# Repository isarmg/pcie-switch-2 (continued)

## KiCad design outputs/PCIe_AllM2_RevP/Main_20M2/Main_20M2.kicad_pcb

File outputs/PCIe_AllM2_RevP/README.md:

# Rev P：120 × 45 mm，20 个竖直 M.2，中心距 6 mm

本版按最新要求将插槽中心间距改为 **6 mm**。在 120 × 45 mm 板框、同面竖直且全部平行的条件下，一排放入 **20 个 M-Key 2280 插槽**；中心坐标为 X=3、9、15……117 mm，Y=23.3 mm。连接器行包络 X=0.825–119.175 mm、Y=11.025–35.575 mm。第 21 个连接器需要 120 mm 的中心跨度，会超出板框，故不保留上一试排的 27 槽数量。

**这是可编辑的布局、网络分配和供电预留草案。大部分线路、CPU 平台供电/时序、固件、阻抗和散热尚未完成，不能直接投产。**

## 2026-10-18：恢复检查点 1（仍不可上电）

- 补齐 M1–M4 的 R3005/R3015/R3025/R3035，100 kΩ 下拉；16 个 F.Cu–In1.Cu 相邻层微孔和 20 段 In1.Cu 铜线，原生连通检查确认每组连接器 pin50 → 电阻 → 本连接器 pin51。**该局部地簇仍未接入输入地，且没有复位释放驱动；不能据此宣称已实现上电复位。** 微孔填孔/叠层工艺尚待板厂确认。
- PCB 与原理图使用 KiCad 10 原生 netlist 精确同步，逐脚双向核验且禁止拆分/合并网络；原始 510 个铜对象的几何与电气归属不变。恢复原理图缺失的厂家链接，padless JHL9580 明确标为仅 PCB 机械占位。
- 修正继承自 E1.S 的错误网类覆盖：512 个数据网络、50 个时钟网络匹配对应草案网类；原有数字规则不变，不代表阻抗已验证。
- 按 TI 引脚表补正 U31/TPS62132、U605/TPS3808 及四颗 TPS565201 的 47 个脚的 ERC 类型，没有新增 PWR_FLAG、NC 标记或排除项。ERC 因真实未供电问题增加到 **47 错误、104 警告**，这些问题仍未解决。
- KiCad 10.0.7 原生 DRC：**几何 0，原理图/PCB parity 0**；499 条未连线是截断报告。全焊盘物理连通检查覆盖 7,558 个编号焊盘形状、7,540 个 ref.pin，确认 **891 个非 NC 网络中有 749 个断网**，不能将 499 当成实际未连线总数。
- U605 的 MR 仍接 1.8 V CPU 信号，而 VDD 为 3.3 V，尚缺正确电压域方案；CPU/PEX 的 1.8 V 电源也没有可证明完整的供电实现。不能照搬另一个设计的复位来源。

最新证据见 [VALIDATION.json](VALIDATION.json) 及 [checkpoint1 原生报告](review_2026-10-18/checkpoint1/REVIEW.json)。旧 STEP、装配图和预览仍是更改前的机械资料，未用于此检查点验收。历史构建器依赖原工作目录，可能覆盖本次 ECO，**不要运行 p_build/p_pipeline 重新生成当前修订**；本次增量脚本与验证器在 scripts/revP 下，详见 [修复记录](ELECTRICAL_REVIEW_2026-10-18.md)。

## 保留布局与槽位

- 主板 120 × 45 mm、32 铜层、名义厚度 1.6 mm，无 E1.S、子板、板间线缆和四角固定孔。
- CPU、PEX88096、USB-C、JHL9580 占位以及原平台器件共 **233 个器件保留原坐标、朝向和安装面**。M.2、新增供电器件以及 40 个端部槽位无源器件按 6 mm 间距重新排布，避免原交流耦合电容与新插槽位置相撞。
- M1/M2 位于 X=3/9 mm，N01–N16 位于 X=15–105 mm，M3/M4 位于 X=111/117 mm。所有插槽 F 面朝上、竖直且方向相同。
- 20 槽各保留 x4 网络分配，CPU 上行 x4；使用主数据 lane 0–83，84–95 共 12 lane 暂空。现有数据 lane 足以分配给全部 20 槽，因此本版没有额外仅供电槽。**没有为新增数量而补画协议铜线；PCIe/时钟大部分仍处于网络分配阶段。** switch 端口固件尚未配置。[Broadcom PEX88096](https://www.broadcom.com/products/pcie-switches-retimers/expressfabric/gen4/pex88096)
- 三颗 9ZXL0851 保留。第三颗仅使用五对输出给 N12–N16，其余三对悬空。CPU 的 ICC/BIOS、SSC/common-clock 和时钟启用配置仍待验证。

## 连接器与机械边界

M.2 和 USB-C 的金属固定脚均为 SMT。USB-C 每个端口的两个塑胶定位孔保留；M.2 取消定位柱孔，避免与背面 BGA 球阵冲突。

M.2 是参考 Amphenol MDT350M01001VT 的 **无定位柱自定义封装草案**，带柱原型号不能不经修改直接安装，实际无柱器件/去柱方案以及触点编号方向均待厂家确认。连接器以 Gen4 为参考，整条通道尚未验证。[Amphenol 参考器件](https://www.amphenol-cs.com/product/mdt350m01001vt.html)

USB-C 的四个 SMT 金属固定脚也是自定义草案，原 USB4160 穿板脚型号不兼容；TB5 连接器和通道资格尚未确认。JHL9580 仍为未核实的机械占位，按用户要求暂缓其电气设计。

switch 面器件高度按 ≤8 mm、连接器面 ≤9 mm；新增 TPSM53604 为最大 4.1 mm 的简化闭合包络。STEP 装配中的 SSD 为竖直的 2280 裸板/元件简化模型，散热器、外接插头和保持架另计。

## 12 V 输入与每槽 4 A 预留

按每槽 **3.3 V / 4 A**，20 槽共 **80 A、264 W** SSD 输出预算。原四个端部插槽保留独立 TPS565201；新增 16 槽各配一套真实 15 针封装的 TPSM53604RDAR、输入/输出电容和反馈分压。

TPSM53604 采用 10 kΩ / 4.32 kΩ，两个 10 µF / 50 V 输入电容、100 nF 旁路和四个 47 µF / 10 V 输出电容。3.3 V 需要至少 52 µF 有效输出电容，188 µF 为标称合计，偏压/温度降容仍未核对。DNC 4/5 独立悬空，V5V 不给外部供电。[TI SNVSBC9C](https://www.ti.com/lit/ds/symlink/tpsm53604.pdf)

输入仍保留 **12 V / 50 A、两个 25 A 支路**的设计目标。按 85% 换算效率及 85 W 平台余量，计算输入预算约 33 A。**模块和供电器件已落位、网络已分配，整板配电铜箔及电源回路仍未布完；输入焊盘、铜厚、线材、保险丝实物、过孔和满载散热能力均未验证。** 自定义 USB 外形供电口仍非 USB/PD，未接通主大电流母线；任何 M.2 电源脚均不接 12 V。

## 电气完成度

CPU 使用 Intel 官方的 2833 个非均匀球位，PEX88096 为真实 1550 球，几何逐球核对。CPU 0.25 mm 焊盘仍待装联图 751493 确认，多路 PMIC、启动时序、EC/BIOS、PDN 尚未完成。

仅保留原 CPU–PEX 的 8 对数据差分线和 1 对参考时钟，共 34 个电容分段铜线网络；其端点连接已经检查。20 槽的大部分协议和电源铜线、等长、阻抗、封装延迟补偿、HDI 工艺和整板 SI 均未完成。新增数据槽的 PERST 暂由下拉保持复位，复位驱动和时序尚未实现，不能宣称可枚举。

KiCad 的几何检查、未连线报告和原理图错误分别保存。短路/间距检查通过不等于电气设计已完成；`ERC.json` 如实保留尚未驱动的电源/控制输入等问题。

## 文件

- `Main_20M2/Main_20M2.kicad_pro`：本机 KiCad 可编辑工程。
- `Main_20M2/Main_20M2.step`：主板与器件；`Assembly_View/Assembly_View.step`：主板与 20 块竖直 2280 简化模型。
- `M2_PORTS.json`、`PORT_PLAN.csv`、`BOM.csv`、`Main_20M2/PIN_MAP.csv`：用途、真实 lane 分配、器件与逐脚网络。
- `CORE_PLACEMENT_BASELINE.json`、`VALIDATION.json`：保留器件、6 mm 间距、球位、原理图/PCB 网络与 lane 分配核验。
- `STEP_VALIDATION.json`：本机 KiCad 导入/再导出 STEP 的结果；`SHA256SUMS.txt`：归档哈希。

历史版本保留：Rev M 为 110 × 45 mm、10 E1.S + 4 M.2；Rev N 为 120 × 45 mm、23 M.2；27 槽的 Rev O 仅为已被本次 6 mm 间距要求取代的试排，未完成电气/STEP核验。本版不生成生产 Gerber 或钻孔包。

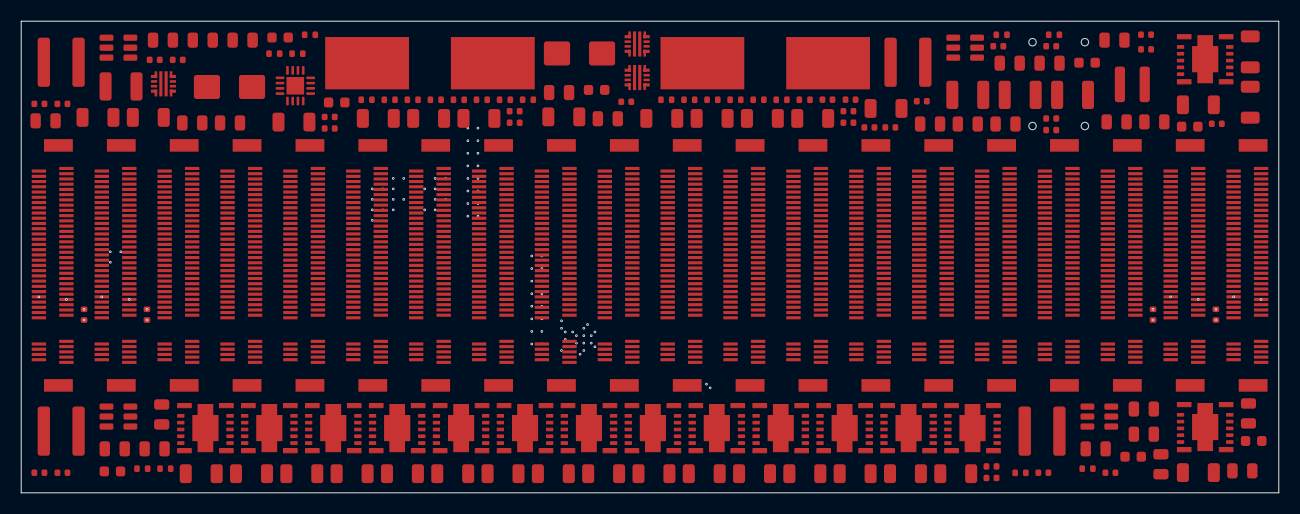
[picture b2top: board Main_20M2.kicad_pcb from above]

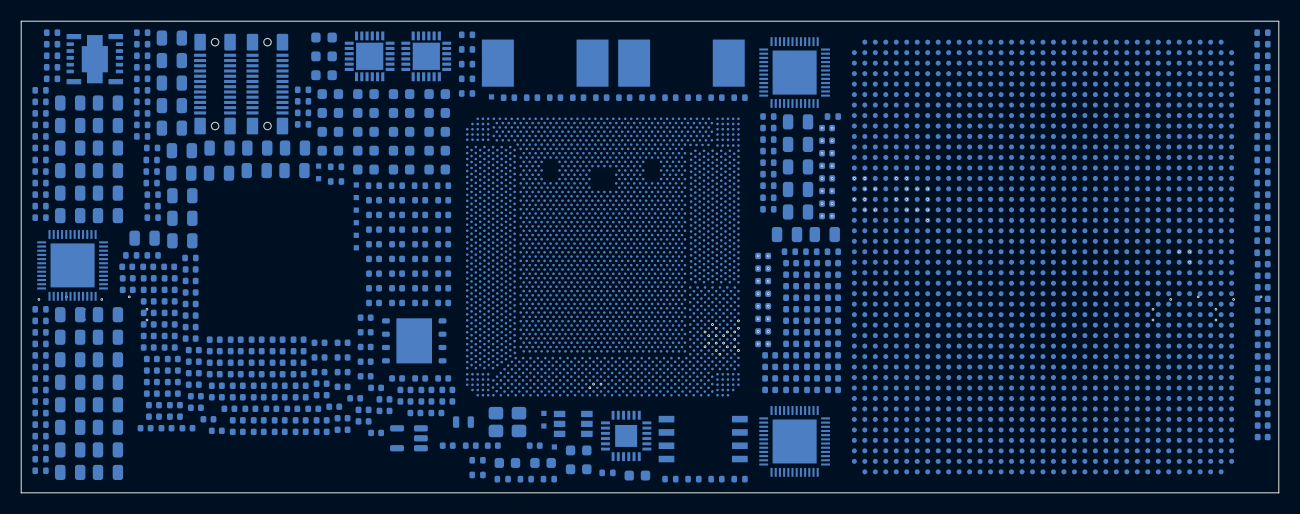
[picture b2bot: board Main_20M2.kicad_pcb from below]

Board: 32 copper layers, 120.0 x 45.0 mm, 647 parts (469 on the bottom side), 787 nets.

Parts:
C1, C2: 10uF 25V X7R; C_1210_3225Metric
C301: 10nF 25V; C_0402_1005Metric
C311: 10uF 25V; C_0805_2012Metric
C312, C3002, C3012, C3022, C3032, C5023, C5043, C5063, C5083, C5103, C5123, C5143, C5163, C5183, C5203, C5223, C5243, C5263, C5283, C5303, C5323: 100nF 50V; C_0402_1005Metric
C313: 3.3nF 25V; C_0402_1005Metric
C314, C315: 47uF 16V; C_1210_3225Metric
C411, C421: 10nF; C_0402_1005Metric
C412, C422: 100nF 50V; C_0603_1608Metric
C701, C720, C721, C722, C723, C724, C725, C726, C727, C728, C730, C731, C732, C733, C734, C735, C736, C737, C738, C742, C6501, C6502, C6503, C6504, C6505, C6506, C6507, C6508, C6509, C6510: 100nF; C_0402_1005Metric
C702, C707, C708: 1uF; C_0402_1005Metric
C703, C704: 18pF DNP TUNE; C_0402_1005Metric
C705, C706: 8.2pF DNP TUNE; C_0402_1005Metric
C709, C710: 100nF RC reset draft; C_0402_1005Metric
C741: 47nF / reset delay; C_0402_1005Metric
C801, C802, C803, C804, C805, C806, C807, C808, C811, C812, C813, C814, C815, C816, C817, C818: 220nF 6.3V X5R; C_0402_1005Metric
C901, C903, C905, C907, C909, C911, C913, C915, C917, C919, C921, C923, C925, C927, C929, C931, C933: 100nF / PDN budget; C_0402_1005Metric
C902, C904, C906, C908, C910, C912, C914, C916, C918, C920, C922, C924, C926, C928, C930, C932, C934: 4.7uF / PDN budget; C_0603_1608Metric
C951, C952, C953, C954, C955, C956, C957, C958, C959, C960: 4.7uF / EDGECAP value pending PDG; C_0603_1608Metric
C965, C966, C967, C968: 1uF / filter value pending PDG; C_0402_1005Metric
C3001, C3011, C3021, C3031: 10uF 25V X7R; C_0805_2012Metric
C3003, C3013, C3023, C3033: 100nF 25V; C_0402_1005Metric
C3004, C3005, C3014, C3015, C3024, C3025, C3034, C3035: 22uF 10V X5R / DC-bias review pending; C_0805_2012Metric
C3006, C3016, C3026, C3036: 1uF 16V; C_0603_1608Metric
C3051, C3052, C3053, C3054, C3055, C3056, C3057, C3058, C3061, C3062, C3063, C3064, C3065, C3066, C3067, C3068, C3071, C3072, C3073, C3074, C3075, C3076, C3077, C3078, C3081, C3082, C3083, C3084, C3085, C3086, C3087, C3088, C6011, C6012, C6013, C6014, C6015, C6016, C6017, C6018, C6021, C6022, C6023, C6024, C6025, C6026, C6027, C6028, C6031, C6032, C6033, C6034, C6035, C6036, C6037, C6038, C6041, C6042, C6043, C6044, C6045, C6046, C6047, C6048, C6051, C6052, C6053, C6054, C6055, C6056, C6057, C6058, C6061, C6062, C6063, C6064, C6065, C6066, C6067, C6068, C6071, C6072, C6073, C6074, C6075, C6076, C6077, C6078, C6081, C6082, C6083, C6084, C6085, C6086, C6087, C6088, C6091, C6092, C6093, C6094, C6095, C6096, C6097, C6098, C6101, C6102, C6103, C6104, C6105, C6106, C6107, C6108, C6111, C6112, C6113, C6114, C6115, C6116, C6117, C6118, C6121, C6122, C6123, C6124, C6125, C6126, C6127, C6128, C6131, C6132, C6133, C6134, C6135, C6136, C6137, C6138, C6141, C6142, C6143, C6144, C6145, C6146, C6147, C6148, C6151, C6152, C6153, C6154, C6155, C6156, C6157, C6158, C6161, C6162, C6163, C6164, C6165, C6166, C6167, C6168: 220nF 16V AC; C_0402_1005Metric
C5021, C5022, C5041, C5042, C5061, C5062, C5081, C5082, C5101, C5102, C5121, C5122, C5141, C5142, C5161, C5162, C5181, C5182, C5201, C5202, C5221, C5222, C5241, C5242, C5261, C5262, C5281, C5282, C5301, C5302, C5321, C5322: 10uF 50V / GRT31CR61H106ME01L; C_1206_3216Metric
C5024, C5025, C5026, C5027, C5044, C5045, C5046, C5047, C5064, C5065, C5066, C5067, C5084, C5085, C5086, C5087, C5104, C5105, C5106, C5107, C5124, C5125, C5126, C5127, C5144, C5145, C5146, C5147, C5164, C5165, C5166, C5167, C5184, C5185, C5186, C5187, C5204, C5205, C5206, C5207, C5224, C5225, C5226, C5227, C5244, C5245, C5246, C5247, C5264, C5265, C5266, C5267, C5284, C5285, C5286, C5287, C5304, C5305, C5306, C5307, C5324, C5325, C5326, C5327: 47uF 10V / GRM21BR61A476ME15L / DC-BIAS REVIEW; C_0805_2012Metric
C6511: 4.7uF 10V; C_0603_1608Metric
C6512: 1uF 10V; C_0603_1608Metric
D1, D2: SMBJ13CA; D_SMB
F1, F2: 25A FUSE / MPN AND THERMAL REVIEW TBD; Littelfuse_456_20A
J11, J12: 12V 25A FEED / DESIGN TARGET, COPPER AND CABLE TBD; WireSolder_2x_8x5_P12
J401: CUSTOM 12V POWER / SMT SHELL DRAFT; USB_C_24P_Vertical_SMT_Shell_7p46_CUSTOM_DRAFT
J402: TB5 PORT / SMT SHELL DRAFT / PART TBD; USB_C_24P_Vertical_SMT_Shell_7p46_CUSTOM_DRAFT
J501: M1 SSD / VERTICAL M-Key 2280 / NO-PEG DRAFT; MKey_Vertical_Gen4_24p2x3p5_NoLocatingPegs_DRAFT
J502: M2 SSD / VERTICAL M-Key 2280 / NO-PEG DRAFT; MKey_Vertical_Gen4_24p2x3p5_NoLocatingPegs_DRAFT
J503: M3 SSD / VERTICAL M-Key 2280 / NO-PEG DRAFT; MKey_Vertical_Gen4_24p2x3p5_NoLocatingPegs_DRAFT
J504: M4 SSD / VERTICAL M-Key 2280 / NO-PEG DRAFT; MKey_Vertical_Gen4_24p2x3p5_NoLocatingPegs_DRAFT
J6001: N01 M-Key 2280 / x4 / NO-PEG DRAFT; MKey_Vertical_Gen4_24p2x3p5_NoLocatingPegs_DRAFT
J6002: N02 M-Key 2280 / x4 / NO-PEG DRAFT; MKey_Vertical_Gen4_24p2x3p5_NoLocatingPegs_DRAFT
J6003: N03 M-Key 2280 / x4 / NO-PEG DRAFT; MKey_Vertical_Gen4_24p2x3p5_NoLocatingPegs_DRAFT
J6004: N04 M-Key 2280 / x4 / NO-PEG DRAFT; MKey_Vertical_Gen4_24p2x3p5_NoLocatingPegs_DRAFT
J6005: N05 M-Key 2280 / x4 / NO-PEG DRAFT; MKey_Vertical_Gen4_24p2x3p5_NoLocatingPegs_DRAFT
J6006: N06 M-Key 2280 / x4 / NO-PEG DRAFT; MKey_Vertical_Gen4_24p2x3p5_NoLocatingPegs_DRAFT
J6007: N07 M-Key 2280 / x4 / NO-PEG DRAFT; MKey_Vertical_Gen4_24p2x3p5_NoLocatingPegs_DRAFT
J6008: N08 M-Key 2280 / x4 / NO-PEG DRAFT; MKey_Vertical_Gen4_24p2x3p5_NoLocatingPegs_DRAFT
J6009: N09 M-Key 2280 / x4 / NO-PEG DRAFT; MKey_Vertical_Gen4_24p2x3p5_NoLocatingPegs_DRAFT
J6010: N10 M-Key 2280 / x4 / NO-PEG DRAFT; MKey_Vertical_Gen4_24p2x3p5_NoLocatingPegs_DRAFT
J6011: N11 M-Key 2280 / x4 / NO-PEG DRAFT; MKey_Vertical_Gen4_24p2x3p5_NoLocatingPegs_DRAFT
J6012: N12 M-Key 2280 / x4 / NO-PEG DRAFT; MKey_Vertical_Gen4_24p2x3p5_NoLocatingPegs_DRAFT
J6013: N13 M-Key 2280 / x4 / NO-PEG DRAFT; MKey_Vertical_Gen4_24p2x3p5_NoLocatingPegs_DRAFT
J6014: N14 M-Key 2280 / x4 / NO-PEG DRAFT; MKey_Vertical_Gen4_24p2x3p5_NoLocatingPegs_DRAFT
J6015: N15 M-Key 2280 / x4 / NO-PEG DRAFT; MKey_Vertical_Gen4_24p2x3p5_NoLocatingPegs_DRAFT
J6016: N16 M-Key 2280 / x4 / NO-PEG DRAFT; MKey_Vertical_Gen4_24p2x3p5_NoLocatingPegs_DRAFT
L31: 2.2uH; L_Coilcraft_XAL4020-XXX
L3001, L3002, L3003, L3004: 2.2uH XAL5030-222MEC; L_Coilcraft_XAL5030-XXX
R301, R411, R421: 76.1k; R_0402_1005Metric
R302, R304, R412, R414, R422, R424, R702, R703, R704, R712, R713, R724, R725, R3002, R3003, R3004, R3012, R3013, R3014, R3022, R3023, R3024, R3032, R3033, R3034, R5013, R5014, R5023, R5024, R5033, R5034, R5043, R5044, R5053, R5054, R5063, R5064, R5073, R5074, R5083, R5084, R5093, R5094, R5103, R5104, R5113, R5114, R5123, R5124, R5133, R5134, R5143, R5144, R5153, R5154, R5163, R5164: 10k; R_0402_1005Metric
R303, R413, R423: 102k; R_0402_1005Metric
R305: 3.32k; R_0402_1005Metric
R311, R401, R402, R710, R711: 100k; R_0402_1005Metric
R415: 665R 1% / ILIM 5.0A; R_0402_1005Metric
R425: 953R 1% / ILIM 3.5A; R_0402_1005Metric
R701: 22R provisional SI tuning; R_0402_1005Metric
R705: 180R 1% / Intel clock topology; R_0402_1005Metric
R706, R707: TBD RCOMP / DNP / Intel PDG required; R_0402_1005Metric
R708, R709: 200R 1%; R_0402_1005Metric
R714, R715, R716: 0R / request clock always on; R_0402_1005Metric
R721, R722: 0R analog supply link / filter pending; R_0402_1005Metric
R730, R731, R732: DNP / filter link pending Intel PDG; R_0402_1005Metric
R740, R741, R742, R743, R744, R745, R746: 10k / Intel required external bias; R_0402_1005Metric
R3001, R3011, R3021, R3031: 33.2k; R_0402_1005Metric
R3005, R3015, R3025, R3035: 100k / RESET BIAS ONLY - RELEASE DRIVER PENDING; R_0402_1005Metric
R5011, R5021, R5031, R5041, R5051, R5061, R5071, R5081, R5091, R5101, R5111, R5121, R5131, R5141, R5151, R5161: 10k 1%; R_0402_1005Metric
R5012, R5022, R5032, R5042, R5052, R5062, R5072, R5082, R5092, R5102, R5112, R5122, R5132, R5142, R5152, R5162: 4.32k 1%; R_0402_1005Metric
R5015, R5025, R5035, R5045, R5055, R5065, R5075, R5085, R5095, R5105, R5115, R5125, R5135, R5145, R5155, R5165: 100k / RESET HELD LOW, DRIVER PENDING; R_0402_1005Metric
R6501: 0R / AVDD FILTER REVIEW; R_0402_1005Metric
TP701: PROBE /CPU_SVID_CLK_1V25; Probe_0p5mm
TP702: PROBE /CPU_SVID_DATA_1V25; Probe_0p5mm
TP703: PROBE /CPU_SVID_ALERT_1V25_N; Probe_0p5mm
TP704: PROBE /CPU_PLT_PWROK; Probe_0p5mm
TP705: PROBE /CPU_SYS_PWROK_1V8; Probe_0p5mm
TP706: PROBE /CPU_RSMRST_N; Probe_0p5mm
TP707: PROBE /CPU_SYS_RESET_1V8_N; Probe_0p5mm
TP708: PROBE /CPU_PWRBTN_1V8_N; Probe_0p5mm
TP709: PROBE /CPU_VCCST_EN_1V8; Probe_0p5mm
TP710: PROBE /CPU_SLP_S3_1V8_N; Probe_0p5mm
TP711: PROBE /CPU_SLP_S4_1V8_N; Probe_0p5mm
TP712: PROBE /CPU_SLP_S5_1V8_N; Probe_0p5mm
U1: Broadcom PEX88096 / SS02-0B00-00; Broadcom_PEX88096_BGA1550_37p5x42p5_1mm
U30, U41, U42: TPS259470ARPWR; TI_RPW0010A_TPS25947
U31: TPS62132RGTR; VQFN-16-1EP_3x3mm_P0.5mm_EP1.68x1.68mm
U501: Intel_JHL9580_MECH_13x13_UNVERIFIED
U502: Intel Core Ultra 7 268V / BGA2833; Intel_Core_Ultra_200V_BGA2833_27p5x27_ExactXY_DraftLands
U601: 9ZXL0851EKILFT / CPU common clock 100MHz; REF_9ZXL0851EKILFT_KU1
U602: 9ZXL0851EKILFT / CPU common clock 100MHz; REF_9ZXL0851EKILFT_KU3
U603: 9FGV0241AKLF / DNP ALTERNATE CLOCK; REF_9FGV0241AKLF_KU2
U604: 9DML0451AKILF / DNP ALTERNATE CLOCK; REF_9DML0451AKILF_KU5
U605: TPS3808G09DBVR / SUPPORT NETWORK PENDING; REF_TPS3808G09DBVR_FU1
U606: W25Q32JWSSIQ_C2980995 / SUPPORT NETWORK PENDING; REF_W25Q32JWSSIQ_FU2
U607: TCA9548ARGER / SUPPORT NETWORK PENDING; REF_TCA9548ARGER_SU1
U701: W25Q256JWPIQ / 1.8V 32MiB BIOS; WSON-8-1EP_6x5mm_P1.27mm_EP3.4x4.3mm
U702: TPS7A0215PDBVR / RTC 1.5V; SOT-23-5
U3001, U3002, U3003, U3004: TPS565201DDCR; SOT-23-6
U5001, U5002, U5003, U5004, U5005, U5006, U5007, U5008, U5009, U5010, U5011, U5012, U5013, U5014, U5015, U5016: TPSM53604RDAR / 12V to 3.3V 4A RESERVATION; Texas_B3QFN-14-1EP_5x5.5mm_P0.65mm
U6501: 9ZXL0851EKILFT / N12-N16 CLOCK, ICC CONFIG PENDING; REF_9ZXL0851EKILFT_KU1
Y701: 38.4MHz crystal / load and ESR selection pending; Crystal_SMD_3225-4Pin_3.2x2.5mm
Y702: 32.768kHz crystal / load and ESR selection pending; Crystal_SMD_2012-2Pin_2.0x1.2mm

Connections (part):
/AUX_12V_PROTECTED: C311.1, C312.1, U30.6, U31.10, U31.11, U31.12, U31.13
/AUX_DVDT: C301.1, U30.7
/AUX_ILM: R305.1, U30.9
/AUX_OV: R303.2, R304.1, U30.2
/AUX_PG: R311.2, U31.4
/AUX_UV: R301.2, R302.1, U30.1
/BUCK_SS: C313.1, U31.9
/BUCK_SW: L31.1, U31.1, U31.2, U31.3
/CLKBUF1_VDDA: C728.1, R721.2, U601.44
/CLKBUF2_VDDA: C738.1, R722.2, U602.44
/CLKBUF3_VDDA: C6512.1, R6501.2, U6501.44
/CPU_ACPRESENT: R741.1, U502.P45
/CPU_BATLOW_N: R740.1, U502.R50
/CPU_CLKBUF1_IN_N: U502.BC2, U601.5
/CPU_CLKBUF1_IN_P: U502.BB1, U601.4
/CPU_CLKBUF2_IN_N: U502.AY4, U602.5
/CPU_CLKBUF2_IN_P: U502.AW3, U602.4
/CPU_CLKBUF3_IN_N: U502.AY2, U6501.5
/CPU_CLKBUF3_IN_P: U502.AW1, U6501.4
/CPU_CLKREQ0_N: R714.1, U502.B55
/CPU_CLKREQ1_N: R715.1, U502.F50
/CPU_CLKREQ2_N: R716.1, U502.E51
/CPU_CLK_RCOMP: R705.1, U502.BG3
/CPU_EPD_ON_LOOP_1V25: U502.AB27, U502.Y27
/CPU_G5_RX0_N: C812.2, U502.DD16
/CPU_G5_RX0_P: C811.2, U502.DE14
/CPU_G5_RX1_N: C814.2, U502.DA18
/CPU_G5_RX1_P: C813.2, U502.CY17
/CPU_G5_RX2_N: C816.2, U502.CY22
/CPU_G5_RX2_P: C815.2, U502.DA21
/CPU_G5_RX3_N: C818.2, U502.DC24
/CPU_G5_RX3_P: C817.2, U502.DD23
/CPU_G5_TX0_N: C802.1, U502.DL16
/CPU_G5_TX0_P: C801.1, U502.DK17
/CPU_G5_TX1_N: C804.1, U502.DH17
/CPU_G5_TX1_P: C803.1, U502.DF18
/CPU_G5_TX2_N: C806.1, U502.DH22
/CPU_G5_TX2_P: C805.1, U502.DF21
/CPU_G5_TX3_N: C808.1, U502.DL23
/CPU_G5_TX3_P: C807.1, U502.DK22
/CPU_PCIE4_RCOMP: R706.1, U502.DL39
/CPU_PCIE5_RCOMP: R707.1, U502.DA1
/CPU_PERST_1V8_N: R725.1, U1.E36, U502.F24, U605.3
/CPU_PEX_RX0_N: C802.2, U1.AF30
/CPU_PEX_RX0_P: C801.2, U1.AF31
/CPU_PEX_RX1_N: C804.2, U1.AG32
/CPU_PEX_RX1_P: C803.2, U1.AG33
/CPU_PEX_RX2_N: C806.2, U1.AH30
/CPU_PEX_RX2_P: C805.2, U1.AH31
/CPU_PEX_RX3_N: C808.2, U1.AJ32
/CPU_PEX_RX3_P: C807.2, U1.AJ33
/CPU_PEX_TX0_N: C812.1, U1.AF35
/CPU_PEX_TX0_P: C811.1, U1.AF36
/CPU_PEX_TX1_N: C814.1, U1.AG36
/CPU_PEX_TX1_P: C813.1, U1.AG37
/CPU_PEX_TX2_N: C816.1, U1.AH35
/CPU_PEX_TX2_P: C815.1, U1.AH36
/CPU_PEX_TX3_N: C818.1, U1.AJ36
/CPU_PEX_TX3_P: C817.1, U1.AJ37
/CPU_PLT_PWROK: R745.1, TP704.1, U502.H13
/CPU_PMCALERT_N: R742.1, U502.F42
/CPU_PWRBTN_1V8_N: R713.1, TP708.1, U502.P47
/CPU_REFCLK_N: U1.AB6, U502.BC4
/CPU_REFCLK_P: U1.AB5, U502.BB3
/CPU_RSMRST_N: R744.1, TP706.1, U502.E13
/CPU_RTCRST_N: C709.1, R710.1, U502.H15
/CPU_RTCX1: C705.1, U502.A12, Y702.1
/CPU_RTCX2: C706.1, U502.A10, Y702.2
/CPU_SLP_S3_1V8_N: TP710.1, U502.M44
/CPU_SLP_S4_1V8_N: TP711.1, U502.L55
/CPU_SLP_S5_1V8_N: TP712.1, U502.P53
/CPU_SPI_CLK_FLASH: R701.2, U701.6
/CPU_SPI_CLK_PAD: R701.1, U502.W13
/CPU_SPI_CS0_N: R702.1, U502.AC17, U701.1
/CPU_SPI_IO0: U502.AA17, U701.5
/CPU_SPI_IO1: U502.AE17, U701.2
/CPU_SPI_IO2: R703.1, U502.W17, U701.3
/CPU_SPI_IO3: R704.1, U502.U13, U701.7
/CPU_SRTCRST_N: C710.1, R711.1, U502.B15
/CPU_SVID_ALERT_1V25_N: TP703.1, U502.F56
/CPU_SVID_CLK_1V25: TP701.1, U502.E55
/CPU_SVID_DATA_1V25: TP702.1, U502.C56
/CPU_SYS_PWROK_1V8: R746.1, TP705.1, U502.H31
/CPU_SYS_RESET_1V8_N: R712.1, TP707.1, U502.M52
/CPU_USB2_RCOMP: R708.1, U502.W1
/CPU_USB32_RCOMP: R709.1, U502.BG1
/CPU_V1P8U_MEM: C901.1, C902.1, U502.AK67, U502.AK70, U502.AL69, U502.AM67, U502.AM70, U502.AP67, U502.AP70, U502.AR69, U502.AT67, U502.AT70, U502.AT73, U502.AT76, U502.AT79, U502.AU69, U502.AU75, U502.AU80, U502.AV67, U502.AV70, U502.AV73, U502.AV76, U502.AV79, U502.AW69, U502.AW72, U502.AW75, U502.AW77, U502.AW80, U502.AY67, U502.AY70, U502.AY73, U502.AY76, U502.AY79, U502.BA72, U502.BA77, U502.BB67, U502.BB70, U502.BB73, U502.BB76, U502.BB79, U502.BC69, U502.BC77, U502.BC80, U502.BD67, U502.BD79, U502.BD82, U502.BD85, U502.BD88, U502.BD90, U502.BD93, U502.BE69, U502.BE80, U502.BE86, U502.BF67, U502.BF79, U502.BF82, U502.BF85, U502.BF88, U502.BF90, U502.BF93, U502.BG69, U502.BG77, U502.BG80, U502.BG83, U502.BG86, U502.BG89, U502.BG92, U502.BH67, U502.BH79, U502.BH82, U502.BH85, U502.BH88, U502.BH90, U502.BH93, U502.BJ77, U502.BK67, U502.BK79, U502.BL69, U502.BL72, U502.BL77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
/CPU_V1P8U_MEM_EDGECAP_0: C951.1, U502.B69, U502.B71
/CPU_V1P8U_MEM_EDGECAP_1: C952.1, U502.AE92, U502.AG92
/CPU_V1P8U_MEM_EDGECAP_2: C953.1, U502.CE92, U502.CG92
/CPU_V1P8U_MEM_EDGECAP_3: C954.1, U502.DK68, U502.DK70
/CPU_VCCGT: C903.1, C904.1, U502.A34, U502.A36, U502.A38, U502.A40, U502.A42, U502.A44, U502.A46, U502.A48, U502.A50, U502.A52, U502.A54, U502.A56, U502.A58, U502.A60, U502.A88, U502.A90, U502.AA34, U502.AA40, U502.AA46, U502.AA51, U502.AA57, U502.AA63, U502.AA69, U502.AA75, U502.AA80, U502.AA86, U502.AB30, U502.AB33, U502.AB36, U502.AB38, U502.AB41, U502.AB44, U502.AB47, U502.AB50, U502.AB53, U502.AB56, U502.AB59, U502.AB62, U502.AB64, U502.AB67, U502.AB70, U502.AB73, U502.AB76, U502.AB79, U502.AB82, U502.AB85, U502.AB88, U502.AB90, U502.AB93, U502.AC31, U502.AC34, U502.AC37, U502.AC40, U502.AC43, U502.AC46, U502.AC49, U502.AC51, U502.AC54, U502.AC57, U502.AC60, U502.AC63, U502.AC66, U502.AC69, U502.AC72, U502.AC75, U502.AC77, U502.AC80, U502.AC83, U502.AC86, U502.AC89, U502.AC92, U502.AD30, U502.AD33, U502.AD36, U502.AD38, U502.AD41, U502.AD44, U502.AD47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
/CPU_VCCL2: C905.1, C906.1, U502.BV41, U502.BV44, U502.BV47, U502.BW40, U502.BW43, U502.BW46
/CPU_VCCPRIM_1P8: C701.1, C702.1, C907.1, C908.1, R702.2, R703.2, R704.2, R712.2, R713.2, R725.2, R730.1, R731.1, R740.2, R741.2, R742.2, R743.2, U502.AR20, U502.AR23, U502.AR26, U502.AT21, U502.AT24, U502.AU20, U502.AU23, U502.AU26, U701.8
/CPU_VCCPRIM_1P8_FLTRA_IN: C966.1, R730.2, U502.BJ20, U502.BL20, U502.BN20
/CPU_VCCPRIM_1P8_FLTRB_CAP: C965.1, U502.CN31, U502.CN34, U502.CP30, U502.CP33
/CPU_VCCPRIM_1P8_FLTRB_IN: C967.1, R731.2, U502.AR17, U502.AT18, U502.AU17
/CPU_VCCPRIM_3P3: C909.1, C910.1, U502.AW17, U502.BA17
/CPU_VCCPRIM_IO: C911.1, C912.1, U502.BB18, U502.BC17, U502.BD18, U502.BE17, U502.BF18, U502.BG17, U502.BH18, U502.BJ17, U502.BK18, U502.BL17, U502.BM18, U502.BN17, U502.BP18, U502.BR17, U502.BT18, U502.BU17, U502.BV18, U502.BW17, U502.BY18, U502.CA17, U502.CB18, U502.CC17, U502.CD18, U502.CE17, U502.CF18, U502.CG17, U502.CH18, U502.CJ17, U502.CK18, U502.CL17, U502.CM18, U502.CN17, U502.CN20, U502.CN23, U502.CN26, U502.CN28, U502.CP18, U502.CP21, U502.CP24, U502.CP27
/CPU_VCCPRIM_VNNAON: C913.1, C914.1, R732.1, U502.AW20, U502.AW23, U502.AW26, U502.AY21, U502.AY24, U502.AY27, U502.BA20, U502.BA26, U502.BB21, U502.BB24, U502.BB27, U502.BC20, U502.BC23, U502.BC26, U502.BD21, U502.BD24, U502.BD27, U502.BE23, U502.BF24, U502.BF27, U502.BG23, U502.BG26, U502.BH21, U502.BH24, U502.BJ23, U502.BJ26, U502.BK24, U502.BL23, U502.BL26, U502.BM24, U502.BN23, U502.BP21, U502.BP24, U502.BR20, U502.BR23, U502.BT21, U502.BT24, U502.BU20, U502.BV21, U502.BV24, U502.BW20, U502.BW23, U502.BY21, U502.BY24, U502.CA23, U502.CB21, U502.CB24, U502.CC20, U502.CC23, U502.CD21, U502.CD24, U502.CE20, U502.CF21, U502.CG20, U502.CG23, U502.CH21, U502.CJ23, U502.CK21, U502.CK24, U502.CK27, U502.CK30, U502.CL20, U502.CL23, U502.CL26, U502.CL28
/CPU_VCCPRIM_VNNAONLV: C915.1, C916.1, U502.BK27, U502.BK30, U502.BL28, U502.BM27, U502.BM30, U502.BN28, U502.BP27, U502.BP30, U502.BR26, U502.BR28, U502.BT27, U502.BT30, U502.BU26, U502.BV27, U502.BV30, U502.BW26, U502.BW28, U502.BY27, U502.BY30, U502.CA28, U502.CB27, U502.CB30, U502.CC26, U502.CC28, U502.CD27, U502.CD30, U502.CE26, U502.CF24, U502.CF27, U502.CF30, U502.CG26, U502.CG28, U502.CH24, U502.CH27, U502.CH30, U502.CJ28
/CPU_VCCPRIM_VNNAON_FLTR: C968.1, R732.2, U502.BE20, U502.BG20
/CPU_VCCRTC: C708.1, C917.1, C918.1, R710.2, R711.2, U502.AN20, U702.5
/CPU_VCCSA: C919.1, C920.1, U502.AU34, U502.AU40, U502.AU46, U502.AU51, U502.AV33, U502.AV36, U502.AV38, U502.AV41, U502.AV44, U502.AV47, U502.AV50, U502.AV53, U502.AV56, U502.AW34, U502.AW37, U502.AW40, U502.AW43, U502.AW46, U502.AW49, U502.AW51, U502.AW54, U502.AY33, U502.AY36, U502.AY38, U502.AY41, U502.AY44, U502.AY47, U502.AY50, U502.AY53, U502.AY56, U502.BA31, U502.BA37, U502.BA43, U502.BA49, U502.BA54, U502.BB33, U502.BB36, U502.BB38, U502.BB41, U502.BB44, U502.BB47, U502.BB50, U502.BB53, U502.BB56, U502.BC31, U502.BC34, U502.BC40, U502.BC43, U502.BC46, U502.BC49, U502.BC51, U502.BC54, U502.BD33, U502.BD36, U502.BD38, U502.BD41, U502.BD44, U502.BD47, U502.BD50, U502.BD53, U502.BD56, U502.BE31, U502.BE34, U502.BE37, U502.BE40, U502.BE46, U502.BE51, U502.BF33, U502.BF36, U502.BF38, U502.BF41, U502.BF44, U502.BF47, U502.BF50, U502.BF53, U502.BF56, U502.BG31, U502.BG34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
/CPU_VCCST: C921.1, C922.1, U502.AU31, U502.AV30
/CPU_VCCST_EN_1V8: TP709.1, U502.M48
/CPU_VCC_ECORE: C923.1, C924.1, U502.BJ40, U502.BJ43, U502.BJ46, U502.BK38, U502.BK41, U502.BK44, U502.BK47, U502.BL43, U502.BM38, U502.BM41, U502.BM44, U502.BM47, U502.BN40, U502.BN43, U502.BN46, U502.BP38, U502.BP41, U502.BP44, U502.BP47, U502.BR43, U502.BT38, U502.BT41, U502.BT44, U502.BT47, U502.BU40, U502.BU43, U502.BU46, U502.BV38
/CPU_VCC_PCORE: C925.1, C926.1, U502.CA40, U502.CA46, U502.CA51, U502.CA57, U502.CA63, U502.CB36, U502.CB38, U502.CB41, U502.CB44, U502.CB47, U502.CB50, U502.CB53, U502.CB56, U502.CB59, U502.CB62, U502.CB64, U502.CC37, U502.CC40, U502.CC43, U502.CC46, U502.CC49, U502.CC51, U502.CC54, U502.CC57, U502.CC60, U502.CC63, U502.CC66, U502.CC69, U502.CC72, U502.CC80, U502.CC83, U502.CC86, U502.CD36, U502.CD38, U502.CD41, U502.CD44, U502.CD47, U502.CD50, U502.CD53, U502.CD56, U502.CD59, U502.CD62, U502.CD64, U502.CD67, U502.CD70, U502.CD82, U502.CD85, U502.CD88, U502.CE37, U502.CE43, U502.CE49, U502.CE54, U502.CE60, U502.CE66, U502.CE72, U502.CE83, U502.CE89, U502.CF36, U502.CF38, U502.CF41, U502.CF44, U502.CF47, U502.CF50, U502.CF53, U502.CF56, U502.CF59, U502.CF62, U502.CF64, U502.CF67, U502.CF70, U502.CF73, U502.CF76, U502.CF79, U502.CF82, U502.CF85, U502.CF88, U502.CG37, U502.CG40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
/CPU_VDD2H: C927.1, C928.1, U502.BJ83, U502.BJ89, U502.BK82, U502.BK85, U502.BK88, U502.BK90, U502.BK93, U502.BL83, U502.BL86, U502.BL89, U502.BL92, U502.BM82, U502.BM85, U502.BM88, U502.BM90, U502.BM93, U502.BN86, U502.BP82, U502.BP85, U502.BP88, U502.BP90, U502.BP93, U502.BR83, U502.BR86, U502.BR89, U502.BR92, U502.BT82, U502.BT85, U502.BT88, U502.BT90, U502.BT93
/CPU_VDD2H_EDGECAP_0: C955.1, U502.B81, U502.B83, U502.B86
/CPU_VDD2H_EDGECAP_1: C956.1, U502.DK80, U502.DK82, U502.DK84
/CPU_VDD2L: C929.1, C930.1, U502.AL72, U502.AL80, U502.AL83, U502.AL86, U502.AL89, U502.AL92, U502.AM73, U502.AM76, U502.AM79, U502.AM82, U502.AM85, U502.AM88, U502.AN72, U502.AN77, U502.AN83, U502.AN89, U502.AN92, U502.AP73, U502.AP76, U502.AP79, U502.AP82, U502.AP85, U502.AP88, U502.AR72, U502.AR75, U502.AR77, U502.AR80, U502.AR83, U502.AR86, U502.AR89, U502.AR92, U502.BU72, U502.BU77, U502.BU83, U502.BU89, U502.BU92, U502.BV73, U502.BV76, U502.BV79, U502.BV82, U502.BV85, U502.BV88, U502.BW72, U502.BW75, U502.BW77, U502.BW80, U502.BW83, U502.BW86, U502.BW89, U502.BW92, U502.BY73, U502.BY76, U502.BY79, U502.BY82, U502.BY85, U502.BY88, U502.CA80, U502.CA86, U502.CA89, U502.CA92, U502.CB82, U502.CB85, U502.CB88
/CPU_VDD2L_EDGECAP_0: C957.1, U502.B73
/CPU_VDD2L_EDGECAP_1: C958.1, U502.DK72
/CPU_VDD2_PWRGOOD_LOOP: U502.AA26, U502.AC26
/CPU_VDDQ: C931.1, C932.1, U502.AT82, U502.AT85, U502.AT88, U502.AT90, U502.AT93, U502.AU86, U502.AV82, U502.AV85, U502.AV88, U502.AV90, U502.AV93, U502.AW83, U502.AW86, U502.AW89, U502.AW92, U502.AY82, U502.AY85, U502.AY88, U502.AY90, U502.AY93, U502.BA83, U502.BA89, U502.BB82, U502.BB85, U502.BB88, U502.BB90, U502.BB93, U502.BC83, U502.BC86, U502.BC89, U502.BC92
/CPU_VDDQ_EDGECAP_0: C959.1, U502.B75, U502.B77, U502.B79
/CPU_VDDQ_EDGECAP_1: C960.1, U502.DK74, U502.DK76, U502.DK78
/CPU_VDDRIO: C933.1, C934.1, U502.AR57, U502.AR60, U502.AR63, U502.AR66, U502.AT59, U502.AT62, U502.AT64, U502.AU57, U502.AU63, U502.AV59, U502.AV62, U502.AV64, U502.AW57, U502.AW60, U502.AW63, U502.AW66, U502.AY59, U502.AY62, U502.AY64, U502.BA60, U502.BA66, U502.BB59, U502.BB62, U502.BB64, U502.BC57, U502.BC60, U502.BC63, U502.BC66, U502.BD59, U502.BD62, U502.BD64, U502.BE57, U502.BE63, U502.BF59, U502.BF62, U502.BF64, U502.BG57, U502.BG60, U502.BG63, U502.BG66, U502.BH59, U502.BH62, U502.BH64, U502.BJ60, U502.BJ66, U502.BK59, U502.BK62, U502.BK64, U502.BL57, U502.BL60, U502.BL63, U502.BM59, U502.BM62, U502.BM64, U502.BN57, U502.BN63, U502.BP59, U502.BP62, U502.BP64, U502.BR57, U502.BR60, U502.BR63, U502.BT59, U502.BT62, U502.BT64, U502.BU60, U502.BU66, U502.BV59, U502.BV62, U502.BV64, U502.BW57, U502.BW60, U502.BW63, U502.BW66, U502.BY59, U502.BY62, U502.BY64
/CPU_WAKE_N: R743.1, U502.P49
/CPU_XTAL_IN: C703.1, U502.M1, Y701.1
/CPU_XTAL_OUT: C704.1, U502.N2, Y701.3
/CUSTOM_12V_RAW: J401.A4, J401.A6, J401.A7, J401.A8, J401.A9, J401.B4, J401.B6, J401.B7, J401.B8, J401.B9
/CUSTOM_DET_A: J401.A5, R401.1
/CUSTOM_DET_B: J401.B5, R402.1
/EXT_41_DVDT: C411.1, U41.7
/EXT_41_ILM: R415.1, U41.9
/EXT_41_OV: R413.2, R414.1, U41.2
/EXT_41_UV: R411.2, R412.1, U41.1
/EXT_42_DVDT: C421.1, U42.7
/EXT_42_ILM: R425.1, U42.9
/EXT_42_OV: R423.2, R424.1, U42.2
/EXT_42_UV: R421.2, R422.1, U42.1
/GND: C1.2, C2.2, C301.2, C311.2, C312.2, C313.2, C314.2, C315.2, C411.2, C412.2, C421.2, C422.2, C701.2, C702.2, C703.2, C704.2, C705.2, C706.2, C707.2, C708.2, C709.2, C710.2, C720.2, C721.2, C722.2, C723.2, C724.2, C725.2, C726.2, C727.2, C728.2, C730.2, C731.2, C732.2, C733.2, C734.2, C735.2, C736.2, C737.2, C738.2, C741.2, C742.2, C901.2, C902.2, C903.2, C904.2, C905.2, C906.2, C907.2, C908.2, C909.2, C910.2, C911.2, C912.2, C913.2, C914.2, C915.2, C916.2, C917.2, C918.2, C919.2, C920.2, C921.2, C922.2, C923.2, C924.2, C925.2, C926.2, C927.2, C928.2, C929.2, C930.2, C931.2, C932.2, C933.2, C934.2, C951.2, C952.2, C953.2, C954.2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
/M1_3V3: C3004.1, C3005.1, C3006.1, J501.2, J501.4, J501.12, J501.14, J501.16, J501.18, J501.70, J501.72, J501.74, L3001.2, R3001.1, R3003.1, R3004.1
/M1_BST: C3003.1, U3001.6
/M1_CLKREQ: J501.52, R3003.2
/M1_CLK_N: J501.53, U602.26
/M1_CLK_P: J501.55, U602.25
/M1_FB: R3001.2, R3002.1, U3001.4
/M1_PERST: J501.50, R3005.1
/M1_RX0_N: J501.41, U1.AJ6
/M1_RX0_P: J501.43, U1.AJ5
/M1_RX1_N: J501.29, U1.AH8
/M1_RX1_P: J501.31, U1.AH7
/M1_RX2_N: J501.17, U1.AG6
/M1_RX2_P: J501.19, U1.AG5
/M1_RX3_N: J501.5, U1.AF8
/M1_RX3_P: J501.7, U1.AF7
/M1_SW: C3003.2, L3001.1, U3001.2
/M1_TX0_N: C3052.1, U1.AJ2
/M1_TX0_N_AC: C3052.2, J501.47
/M1_TX0_P: C3051.1, U1.AJ1
/M1_TX0_P_AC: C3051.2, J501.49
/M1_TX1_N: C3054.1, U1.AH3
/M1_TX1_N_AC: C3054.2, J501.35
/M1_TX1_P: C3053.1, U1.AH2
/M1_TX1_P_AC: C3053.2, J501.37
/M1_TX2_N: C3056.1, U1.AG2
/M1_TX2_N_AC: C3056.2, J501.23
/M1_TX2_P: C3055.1, U1.AG1
/M1_TX2_P_AC: C3055.2, J501.25
/M1_TX3_N: C3058.1, U1.AF3
/M1_TX3_N_AC: C3058.2, J501.11
/M1_TX3_P: C3057.1, U1.AF2
/M1_TX3_P_AC: C3057.2, J501.13
/M1_WAKE: J501.54, R3004.2
/M2_3V3: C3014.1, C3015.1, C3016.1, J502.2, J502.4, J502.12, J502.14, J502.16, J502.18, J502.70, J502.72, J502.74, L3002.2, R3011.1, R3013.1, R3014.1
/M2_12V_L: C3001.1, C3002.1, C3011.1, C3012.1, U41.6, U3001.3, U3001.5, U3002.3, U3002.5
/M2_12V_R: C3021.1, C3022.1, C3031.1, C3032.1, U42.6, U3003.3, U3003.5, U3004.3, U3004.5
/M2_BST: C3013.1, U3002.6
/M2_CLKREQ: J502.52, R3013.2
/M2_CLK_N: J502.53, U602.29
/M2_CLK_P: J502.55, U602.28
/M2_FB: R3011.2, R3012.1, U3002.4
/M2_PERST: J502.50, R3015.1
/M2_RX0_N: J502.41, U1.R32
/M2_RX0_P: J502.43, U1.R33
/M2_RX1_N: J502.29, U1.P33
/M2_RX1_P: J502.31, U1.P34
/M2_RX2_N: J502.17, U1.N32
/M2_RX2_P: J502.19, U1.N33
/M2_RX3_N: J502.5, U1.M33
/M2_RX3_P: J502.7, U1.M34
/M2_SW: C3013.2, L3002.1, U3002.2
/M2_TX0_N: C3062.1, U1.R36
/M2_TX0_N_AC: C3062.2, J502.47
/M2_TX0_P: C3061.1, U1.R37
/M2_TX0_P_AC: C3061.2, J502.49
/M2_TX1_N: C3064.1, U1.P36
/M2_TX1_N_AC: C3064.2, J502.35
/M2_TX1_P: C3063.1, U1.P37
/M2_TX1_P_AC: C3063.2, J502.37
/M2_TX2_N: C3066.1, U1.N36
/M2_TX2_N_AC: C3066.2, J502.23
/M2_TX2_P: C3065.1, U1.N37
/M2_TX2_P_AC: C3065.2, J502.25
/M2_TX3_N: C3068.1, U1.M36
/M2_TX3_N_AC: C3068.2, J502.11
/M2_TX3_P: C3067.1, U1.M37
/M2_TX3_P_AC: C3067.2, J502.13
/M2_WAKE: J502.54, R3014.2
/M3_3V3: C3024.1, C3025.1, C3026.1, J503.2, J503.4, J503.12, J503.14, J503.16, J503.18, J503.70, J503.72, J503.74, L3003.2, R3021.1, R3023.1, R3024.1
/M3_BST: C3023.1, U3003.6
/M3_CLKREQ: J503.52, R3023.2
/M3_CLK_N: J503.53, U602.33
/M3_CLK_P: J503.55, U602.32
/M3_FB: R3021.2, R3022.1, U3003.4
/M3_PERST: J503.50, R3025.1
/M3_RX0_N: J503.41, U1.E34
/M3_RX0_P: J503.43, U1.D34
/M3_RX1_N: J503.29, U1.F33
/M3_RX1_P: J503.31, U1.E33
/M3_RX2_N: J503.17, U1.E32
/M3_RX2_P: J503.19, U1.D32
/M3_RX3_N: J503.5, U1.F31
/M3_RX3_P: J503.7, U1.E31
/M3_SW: C3023.2, L3003.1, U3003.2
/M3_TX0_N: C3072.1, U1.B34
/M3_TX0_N_AC: C3072.2, J503.47
/M3_TX0_P: C3071.1, U1.A34
/M3_TX0_P_AC: C3071.2, J503.49
/M3_TX1_N: C3074.1, U1.B33
/M3_TX1_N_AC: C3074.2, J503.35
/M3_TX1_P: C3073.1, U1.A33
/M3_TX1_P_AC: C3073.2, J503.37
/M3_TX2_N: C3076.1, U1.B32
/M3_TX2_N_AC: C3076.2, J503.23
/M3_TX2_P: C3075.1, U1.A32
/M3_TX2_P_AC: C3075.2, J503.25
/M3_TX3_N: C3078.1, U1.B31
/M3_TX3_N_AC: C3078.2, J503.11
/M3_TX3_P: C3077.1, U1.A31
/M3_TX3_P_AC: C3077.2, J503.13
/M3_WAKE: J503.54, R3024.2
/M4_3V3: C3034.1, C3035.1, C3036.1, J504.2, J504.4, J504.12, J504.14, J504.16, J504.18, J504.70, J504.72, J504.74, L3004.2, R3031.1, R3033.1, R3034.1
/M4_BST: C3033.1, U3004.6
/M4_CLKREQ: J504.52, R3033.2
/M4_CLK_N: J504.53, U602.36
/M4_CLK_P: J504.55, U602.35
/M4_FB: R3031.2, R3032.1, U3004.4
/M4_PERST: J504.50, R3035.1
/M4_RX0_N: J504.41, U1.L32
/M4_RX0_P: J504.43, U1.L33
/M4_RX1_N: J504.29, U1.K33
/M4_RX1_P: J504.31, U1.K34
/M4_RX2_N: J504.17, U1.J32
/M4_RX2_P: J504.19, U1.J33
/M4_RX3_N: J504.5, U1.H33
/M4_RX3_P: J504.7, U1.H34
/M4_SW: C3033.2, L3004.1, U3004.2
/M4_TX0_N: C3082.1, U1.L36
/M4_TX0_N_AC: C3082.2, J504.47
/M4_TX0_P: C3081.1, U1.L37
/M4_TX0_P_AC: C3081.2, J504.49
/M4_TX1_N: C3084.1, U1.K36
/M4_TX1_N_AC: C3084.2, J504.35
/M4_TX1_P: C3083.1, U1.K37
/M4_TX1_P_AC: C3083.2, J504.37
/M4_TX2_N: C3086.1, U1.J36
/M4_TX2_N_AC: C3086.2, J504.23
/M4_TX2_P: C3085.1, U1.J37
/M4_TX2_P_AC: C3085.2, J504.25
/M4_TX3_N: C3088.1, U1.H36
/M4_TX3_N_AC: C3088.2, J504.11
/M4_TX3_P: C3087.1, U1.H37
/M4_TX3_P_AC: C3087.2, J504.13
/M4_WAKE: J504.54, R3034.2
/N01_3V3: C5024.1, C5025.1, C5026.1, C5027.1, J6001.2, J6001.4, J6001.12, J6001.14, J6001.16, J6001.18, J6001.70, J6001.72, J6001.74, R5011.1, R5013.1, R5014.1, U5001.7, U5001.8
/N01_CLKREQ: J6001.52, R5013.2
/N01_CLK_N: J6001.53, U601.17
/N01_CLK_P: J6001.55, U601.16
/N01_FB: R5011.2, R5012.1, U5001.9
/N01_PERST: J6001.50, R5015.1
/N01_RX0_N: J6001.41, U1.AK30
/N01_RX0_P: J6001.43, U1.AK31
/N01_RX1_N: J6001.29, U1.AL32
/N01_RX1_P: J6001.31, U1.AL33
/N01_RX2_N: J6001.17, U1.AM30
/N01_RX2_P: J6001.19, U1.AM31
/N01_RX3_N: J6001.5, U1.AN32
/N01_RX3_P: J6001.7, U1.AN33
/N01_TX0_N: C6012.1, U1.AK35
/N01_TX0_N_AC: C6012.2, J6001.47
/N01_TX0_P: C6011.1, U1.AK36
/N01_TX0_P_AC: C6011.2, J6001.49
/N01_TX1_N: C6014.1, U1.AL36
/N01_TX1_N_AC: C6014.2, J6001.35
/N01_TX1_P: C6013.1, U1.AL37
/N01_TX1_P_AC: C6013.2, J6001.37
/N01_TX2_N: C6016.1, U1.AM35
/N01_TX2_N_AC: C6016.2, J6001.23
/N01_TX2_P: C6015.1, U1.AM36
/N01_TX2_P_AC: C6015.2, J6001.25
/N01_TX3_N: C6018.1, U1.AN36
/N01_TX3_N_AC: C6018.2, J6001.11
/N01_TX3_P: C6017.1, U1.AN37
/N01_TX3_P_AC: C6017.2, J6001.13
/N01_WAKE: J6001.54, R5014.2
/N02_3V3: C5044.1, C5045.1, C5046.1, C5047.1, J6002.2, J6002.4, J6002.12, J6002.14, J6002.16, J6002.18, J6002.70, J6002.72, J6002.74, R5021.1, R5023.1, R5024.1, U5002.7, U5002.8
/N02_CLKREQ: J6002.52, R5023.2
/N02_CLK_N: J6002.53, U601.22
/N02_CLK_P: J6002.55, U601.21
/N02_FB: R5021.2, R5022.1, U5002.9
/N02_PERST: J6002.50, R5025.1
/N02_RX0_N: J6002.41, U1.AR34
/N02_RX0_P: J6002.43, U1.AT34
/N02_RX1_N: J6002.29, U1.AU33
/N02_RX1_P: J6002.31, U1.AV33
/N02_RX2_N: J6002.17, U1.AR32
/N02_RX2_P: J6002.19, U1.AT32
/N02_RX3_N: J6002.5, U1.AU31
/N02_RX3_P: J6002.7, U1.AV31
/N02_TX0_N: C6022.1, U1.AY34
/N02_TX0_N_AC: C6022.2, J6002.47
/N02_TX0_P: C6021.1, U1.BA34
/N02_TX0_P_AC: C6021.2, J6002.49
/N02_TX1_N: C6024.1, U1.BA33
/N02_TX1_N_AC: C6024.2, J6002.35
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
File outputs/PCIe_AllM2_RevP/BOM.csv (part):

Board,Reference,Value,Footprint,Side,X_mm,Y_mm,Rotation_deg,Height_envelope_mm,DNP,Mechanical_only
Main_20M2,C1,10uF 25V X7R,C_1210_3225Metric,F,95.325,7.025,0.0,,False,False
Main_20M2,C2,10uF 25V X7R,C_1210_3225Metric,F,100.325,7.025,0.0,,False,False
Main_20M2,C3001,10uF 25V X7R,C_0805_2012Metric,F,13.525,1.805,0.0,1.45,False,False
Main_20M2,C3002,100nF 50V,C_0402_1005Metric,F,12.735,3.685,0.0,0.55,False,False
Main_20M2,C3003,100nF 25V,C_0402_1005Metric,F,14.935,3.685,0.0,0.55,False,False
Main_20M2,C3004,22uF 10V X5R / DC-bias review pending,C_0805_2012Metric,F,17.325,1.805,0.0,1.45,False,False
Main_20M2,C3005,22uF 10V X5R / DC-bias review pending,C_0805_2012Metric,F,21.125,1.805,0.0,1.45,False,False
Main_20M2,C3006,1uF 16V,C_0603_1608Metric,F,24.705,1.555,0.0,0.9,False,False
Main_20M2,C301,10nF 25V,C_0402_1005Metric,F,3.935,7.885,0.0,,False,False
Main_20M2,C3011,10uF 25V X7R,C_0805_2012Metric,F,8.925,40.805,0.0,1.45,False,False
Main_20M2,C3012,100nF 50V,C_0402_1005Metric,F,1.735,43.085,0.0,0.55,False,False
Main_20M2,C3013,100nF 25V,C_0402_1005Metric,F,3.935,43.085,0.0,0.55,False,False
Main_20M2,C3014,22uF 10V X5R / DC-bias review pending,C_0805_2012Metric,F,12.725,40.805,0.0,1.45,False,False
Main_20M2,C3015,22uF 10V X5R / DC-bias review pending,C_0805_2012Metric,F,13.405,37.525,90.0,1.45,False,False
Main_20M2,C3016,1uF 16V,C_0603_1608Metric,F,8.705,42.955,0.0,0.9,False,False
Main_20M2,C3021,10uF 25V X7R,C_0805_2012Metric,F,104.325,1.805,0.0,1.45,False,False
Main_20M2,C3022,100nF 50V,C_0402_1005Metric,F,107.335,1.285,0.0,0.55,False,False
Main_20M2,C3023,100nF 25V,C_0402_1005Metric,F,107.335,2.685,0.0,0.55,False,False
Main_20M2,C3024,22uF 10V X5R / DC-bias review pending,C_0805_2012Metric,F,94.325,4.005,0.0,1.45,False,False
Main_20M2,C3025,22uF 10V X5R / DC-bias review pending,C_0805_2012Metric,F,98.125,4.005,0.0,1.45,False,False
Main_20M2,C3026,1uF 16V,C_0603_1608Metric,F,101.705,3.955,0.0,0.9,False,False
Main_20M2,C3031,10uF 25V X7R,C_0805_2012Metric,F,107.125,37.005,0.0,1.45,False,False
Main_20M2,C3032,100nF 50V,C_0402_1005Metric,F,97.535,43.085,0.0,0.55,False,False
Main_20M2,C3033,100nF 25V,C_0402_1005Metric,F,103.935,43.085,0.0,0.55,False,False
Main_20M2,C3034,22uF 10V X5R / DC-bias review pending,C_0805_2012Metric,F,107.125,39.405,0.0,1.45,False,False
Main_20M2,C3035,22uF 10V X5R / DC-bias review pending,C_0805_2012Metric,F,102.525,40.805,0.0,1.45,False,False
Main_20M2,C3036,1uF 16V,C_0603_1608Metric,F,106.105,41.555,0.0,0.9,False,False
Main_20M2,C3051,220nF 16V AC,C_0402_1005Metric,B,103.835,23.685,0.0,0.55,False,False
Main_20M2,C3052,220nF 16V AC,C_0402_1005Metric,B,42.535,24.185,0.0,0.55,False,False
Main_20M2,C3053,220nF 16V AC,C_0402_1005Metric,B,44.535,24.185,0.0,0.55,False,False
Main_20M2,C3054,220nF 16V AC,C_0402_1005Metric,B,46.535,24.185,0.0,0.55,False,False
Main_20M2,C3055,220nF 16V AC,C_0402_1005Metric,B,1.535,24.285,0.0,0.55,False,False
Main_20M2,C3056,220nF 16V AC,C_0402_1005Metric,B,99.335,39.185,0.0,0.55,False,False
Main_20M2,C3057,220nF 16V AC,C_0402_1005Metric,B,105.835,24.535,0.0,0.55,False,False
Main_20M2,C3058,220nF 16V AC,C_0402_1005Metric,B,107.835,24.535,0.0,0.55,False,False
Main_20M2,C3061,220nF 16V AC,C_0402_1005Metric,B,42.535,23.085,0.0,0.55,False,False
Main_20M2,C3062,220nF 16V AC,C_0402_1005Metric,B,44.535,23.085,0.0,0.55,False,False
Main_20M2,C3063,220nF 16V AC,C_0402_1005Metric,B,46.535,23.085,0.0,0.55,False,False
Main_20M2,C3064,220nF 16V AC,C_0402_1005Metric,B,1.535,23.185,0.0,0.55,False,False
Main_20M2,C3065,220nF 16V AC,C_0402_1005Metric,B,105.885,23.435,0.0,0.55,False,False
Main_20M2,C3066,220nF 16V AC,C_0402_1005Metric,B,93.335,38.085,0.0,0.55,False,False
Main_20M2,C3067,220nF 16V AC,C_0402_1005Metric,B,107.885,23.435,0.0,0.55,False,False
Main_20M2,C3068,220nF 16V AC,C_0402_1005Metric,B,109.885,23.435,0.0,0.55,False,False
Main_20M2,C3071,220nF 16V AC,C_0402_1005Metric,B,95.335,38.085,0.0,0.55,False,False
Main_20M2,C3072,220nF 16V AC,C_0402_1005Metric,B,97.335,38.085,0.0,0.55,False,False
Main_20M2,C3073,220nF 16V AC,C_0402_1005Metric,B,99.335,38.085,0.0,0.55,False,False
Main_20M2,C3074,220nF 16V AC,C_0402_1005Metric,B,87.335,38.185,0.0,0.55,False,False
Main_20M2,C3075,220nF 16V AC,C_0402_1005Metric,B,1.535,38.585,0.0,0.55,False,False
Main_20M2,C3076,220nF 16V AC,C_0402_1005Metric,B,86.135,39.285,0.0,0.55,False,False
Main_20M2,C3077,220nF 16V AC,C_0402_1005Metric,B,104.135,38.835,0.0,0.55,False,False
Main_20M2,C3078,220nF 16V AC,C_0402_1005Metric,B,106.135,38.835,0.0,0.55,False,False
Main_20M2,C3081,220nF 16V AC,C_0402_1005Metric,B,108.135,38.835,0.0,0.55,False,False
Main_20M2,C3082,220nF 16V AC,C_0402_1005Metric,B,89.335,38.985,0.0,0.55,False,False
Main_20M2,C3083,220nF 16V AC,C_0402_1005Metric,B,101.335,39.085,0.0,0.55,False,False
Main_20M2,C3084,220nF 16V AC,C_0402_1005Metric,B,91.335,39.185,0.0,0.55,False,False
Main_20M2,C3085,220nF 16V AC,C_0402_1005Metric,B,93.335,39.185,0.0,0.55,False,False
Main_20M2,C3086,220nF 16V AC,C_0402_1005Metric,B,1.535,39.685,0.0,0.55,False,False
Main_20M2,C3087,220nF 16V AC,C_0402_1005Metric,B,95.335,39.185,0.0,0.55,False,False
Main_20M2,C3088,220nF 16V AC,C_0402_1005Metric,B,97.335,39.185,0.0,0.55,False,False
Main_20M2,C311,10uF 25V,C_0805_2012Metric,F,51.325,6.805,0.0,,False,False
Main_20M2,C312,100nF 50V,C_0402_1005Metric,F,1.735,7.885,0.0,,False,False
Main_20M2,C313,3.3nF 25V,C_0402_1005Metric,F,79.135,7.485,0.0,,False,False
Main_20M2,C314,47uF 16V,C_1210_3225Metric,F,9.525,6.225,0.0,,False,False
Main_20M2,C315,47uF 16V,C_1210_3225Metric,F,90.325,7.025,0.0,,False,False
Main_20M2,C411,10nF,C_0402_1005Metric,F,76.935,7.485,0.0,0.55,False,False
Main_20M2,C412,100nF 50V,C_0603_1608Metric,F,30.105,7.755,0.0,0.9,False,False
Main_20M2,C421,10nF,C_0402_1005Metric,F,57.735,7.685,0.0,0.55,False,False
Main_20M2,C422,100nF 50V,C_0603_1608Metric,F,54.905,6.555,0.0,0.9,False,False
Main_20M2,C5021,10uF 50V / GRT31CR61H106ME01L,C_1206_3216Metric,F,112.325,7.975,0.0,1.8,False,False
Main_20M2,C5022,10uF 50V / GRT31CR61H106ME01L,C_1206_3216Metric,F,112.325,43.075,0.0,1.8,False,False
Main_20M2,C5023,100nF 50V,C_0402_1005Metric,F,92.585,42.485,0.0,0.55,False,False
Main_20M2,C5024,47uF 10V / GRM21BR61A476ME15L / DC-BIAS REVIEW,C_0805_2012Metric,F,116.525,42.905,0.0,1.45,False,False
Main_20M2,C5025,47uF 10V / GRM21BR61A476ME15L / DC-BIAS REVIEW,C_0805_2012Metric,F,55.975,9.305,0.0,1.45,False,False
Main_20M2,C5026,47uF 10V / GRM21BR61A476ME15L / DC-BIAS REVIEW,C_0805_2012Metric,F,2.325,9.504999,0.0,1.45,False,False
Main_20M2,C5027,47uF 10V / GRM21BR61A476ME15L / DC-BIAS REVIEW,C_0805_2012Metric,F,104.525,9.605,0.0,1.45,False,False
Main_20M2,C5041,10uF 50V / GRT31CR61H106ME01L,C_1206_3216Metric,F,82.525,8.325,0.0,1.8,False,False
Main_20M2,C5042,10uF 50V / GRT31CR61H106ME01L,C_1206_3216Metric,F,51.775,9.125,0.0,1.8,False,False
Main_20M2,C5043,100nF 50V,C_0402_1005Metric,F,92.585,43.585,0.0,0.55,False,False
Main_20M2,C5044,47uF 10V / GRM21BR61A476ME15L / DC-BIAS REVIEW,C_0805_2012Metric,F,108.125,9.605,0.0,1.45,False,False
Main_20M2,C5045,47uF 10V / GRM21BR61A476ME15L / DC-BIAS REVIEW,C_0805_2012Metric,F,16.325,9.705,0.0,1.45,False,False
Main_20M2,C5046,47uF 10V / GRM21BR61A476ME15L / DC-BIAS REVIEW,C_0805_2012Metric,F,19.925,9.705,0.0,1.45,False,False
Main_20M2,C5047,47uF 10V / GRM21BR61A476ME15L / DC-BIAS REVIEW,C_0805_2012Metric,F,86.725,9.805,0.0,1.45,False,False
Main_20M2,C5061,10uF 50V / GRT31CR61H106ME01L,C_1206_3216Metric,F,7.325,9.175,0.0,1.8,False,False
Main_20M2,C5062,10uF 50V / GRT31CR61H106ME01L,C_1206_3216Metric,F,12.125,9.175,0.0,1.8,False,False
Main_20M2,C5063,100nF 50V,C_0402_1005Metric,F,114.085,9.785,0.0,0.55,False,False
Main_20M2,C5064,47uF 10V / GRM21BR61A476ME15L / DC-BIAS REVIEW,C_0805_2012Metric,F,90.325,9.805,0.0,1.45,False,False
Main_20M2,C5065,47uF 10V / GRM21BR61A476ME15L / DC-BIAS REVIEW,C_0805_2012Metric,F,93.925,9.805,0.0,1.45,False,False
Main_20M2,C5066,47uF 10V / GRM21BR61A476ME15L / DC-BIAS REVIEW,C_0805_2012Metric,F,117.105,37.425,90.0,1.45,False,False
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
